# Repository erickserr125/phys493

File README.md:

# phys493
KI-CAD files for photodiode PCB &amp; schematics. Also providing documentation

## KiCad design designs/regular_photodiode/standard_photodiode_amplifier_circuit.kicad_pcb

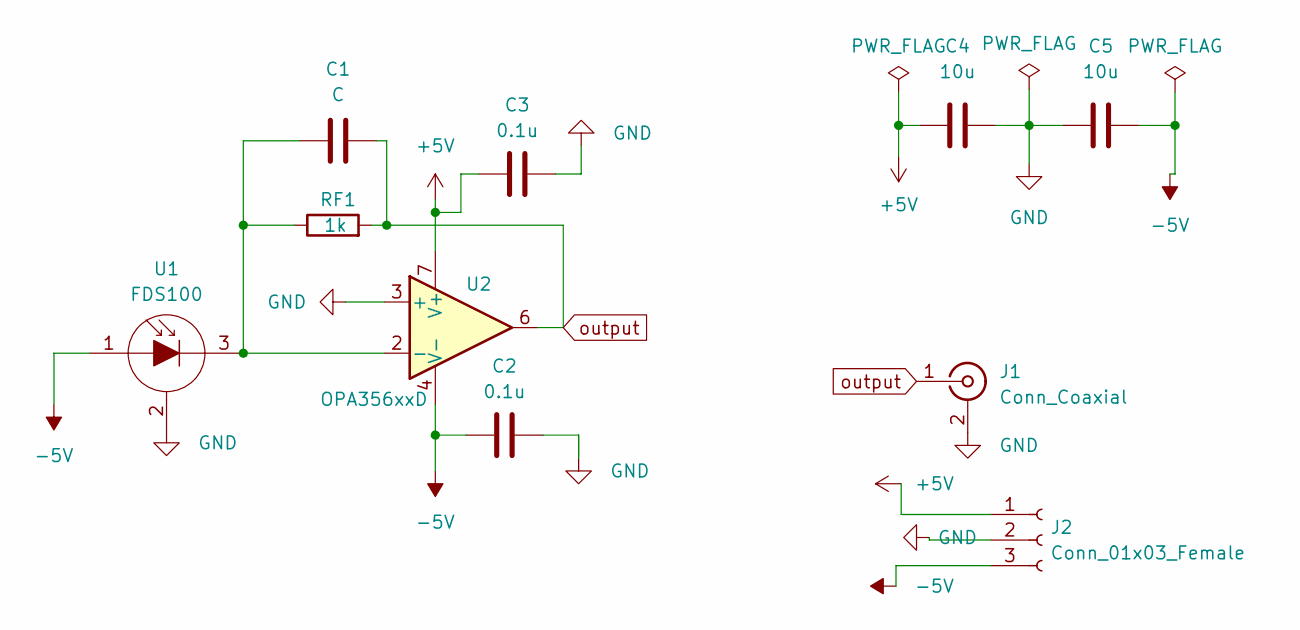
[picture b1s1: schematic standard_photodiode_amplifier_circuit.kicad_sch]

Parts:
C1: C; C_1206_3216Metric
C2, C3: 0.1u; C_1206_3216Metric
C4, C5: 10u; C_1206_3216Metric
J1: Conn_Coaxial; SMA_Amphenol_901-144_Vertical
J2: Conn_01x03_Female; Molex_KK-254_AE-6410-03A_1x03_P2.54mm_Vertical
RF1: 1k; R_1206_3216Metric
U1: FDS100; TO-33-4
U2: OPA356xxD; SOIC-8_3.9x4.9mm_P1.27mm

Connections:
+5V: C3.1, C4.1, J2.1, U2.7 (V+)
-5V: C2.1, C5.2, J2.3, U1.1, U2.4 (V-)
GND: C2.2, C3.2, C4.2, C5.1, J1.2 (Ext), J2.2, U1.2, U2.3 (+)
unnamed: C1.1, RF1.1, U1.3, U2.2 (-)
output: C1.2, J1.1 (In), RF1.2, U2.6

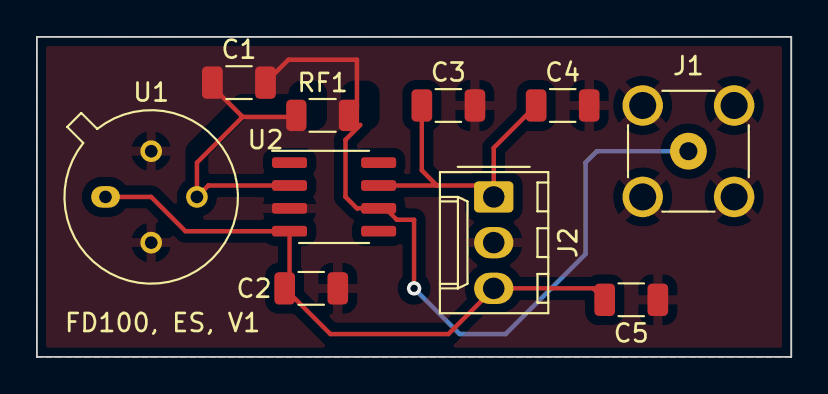
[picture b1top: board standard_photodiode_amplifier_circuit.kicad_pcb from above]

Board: 2 copper layers, 41.9 x 17.8 mm, 10 parts (0 on the bottom side), 5 nets.

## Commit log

2023-01-13 Adding PCB and schematic files for simple PD
    PD= Photodiode
2023-01-13 Adding my notes thus far (1/13/22)
2023-01-13 Rename standard_photodiode_amplifier_circuit.kicad_pcb to designs/regular_photodiode/standard_photodiode_amplifier_circuit.kicad_pcb
2023-01-13 Rename standard_photodiode_amplifier_circuit.kicad_sch to designs/regular_photodiode/standard_photodiode_amplifier_circuit.kicad_sch
2023-01-13 Added notes from my visit on 1/12/22
    Stayed approximately from 1:00 to 4:30pm
2023-01-19 Finished quadratic photodiode circuit
    Missing quadratic photodiode input & missing footprint assignments. Also requires verification by Dr. Zhou
2023-01-24 Updated Notes for last week's work (1/17 & 1/19)
2023-01-26 Updated schematic with better amplifier/pd
    Used a circuit which stores four amplifiers and finally added the quadrant photodiode schematic.
2023-01-27 Added Ki-Cad PRO file for editing schematic
2023-01-27 Added kicad-PRO file for editing quad-PD schematic
2023-01-27 Creating folder with filler.txt
2023-01-27 Uploaded images for the week of January 16th
    I will include these files in the .md report for the week of the 16th
2023-01-27 remove filler file
2023-01-27 Adding schematic of quad-pd for report
2023-01-27 Updated latest notes with relevant images
2023-01-27 Removed image formatting
2023-01-31 PCB Version 1 (Using Dr. Zhou's schematic)
    I used Through-Hole Vias to design the PCB. It may or may not be accepted by our manufacturer. More versions to come if there are any issues
2023-02-02 Updated PCB to V1 with Dr. Zhou's changes
2023-02-02 Latest schematic for the quadrant pd circuit
2023-02-02 Latest Quadrant PD PCB design
2023-02-02 Uploaded Derivation of Balanced PD schematic
2023-02-02 Notes for the past two weeks: 1/24,1/26,1/30,2/2,2/3
2023-02-02 Finished first balanced pd design
2023-02-07 Updated Balanced PD PCB design(Slight Issue)
    Having issues with filling the PCB board so that the ground is connected together. Also have warnings regarding the silkscreen. Otherwise, the PCB design is fine.
2023-02-07 Uploaded images of simpler balanced PD
    Unsure how to interpret the balanced PD schematics I see online. It seems that some schematics suggest using a transimpedance amplifier followed by simple subtraction (as seen in the other balanced P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
2023-02-07 Uploaded Simpler Balanced PD(Unsure)
    The schematic I used draws from the schematics I found online (uploaded in the images folder under week 6, 2/7/2023). I can't fully interpret them, and some images suggest using the original schemati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
2023-02-14 Added simpler balanced PD schematic for reference
2023-02-14 PCB board progress uploaded.
2023-02-14 Notes for Week 7 (2/7,2/9)
2023-02-15 Updated balanced PD with completed schematic & PCB
    This should be the final version that we print out.
2023-02-18 create video folder
2023-02-18 Uploaded working video of the photodiode circuit
    The photodiode circuit gave out right after this video since the amplifier could not withstand more than 5V of difference between the positive and negative terminals. We will use a new amplifier.
2023-02-18 Finished PCB/schematic for simple balanced pd
    The KiCad files for this balanced PD schematic/PCB can be found in the designs folder.
2023-02-18 New notes for week 8 (2/15,2/16)
